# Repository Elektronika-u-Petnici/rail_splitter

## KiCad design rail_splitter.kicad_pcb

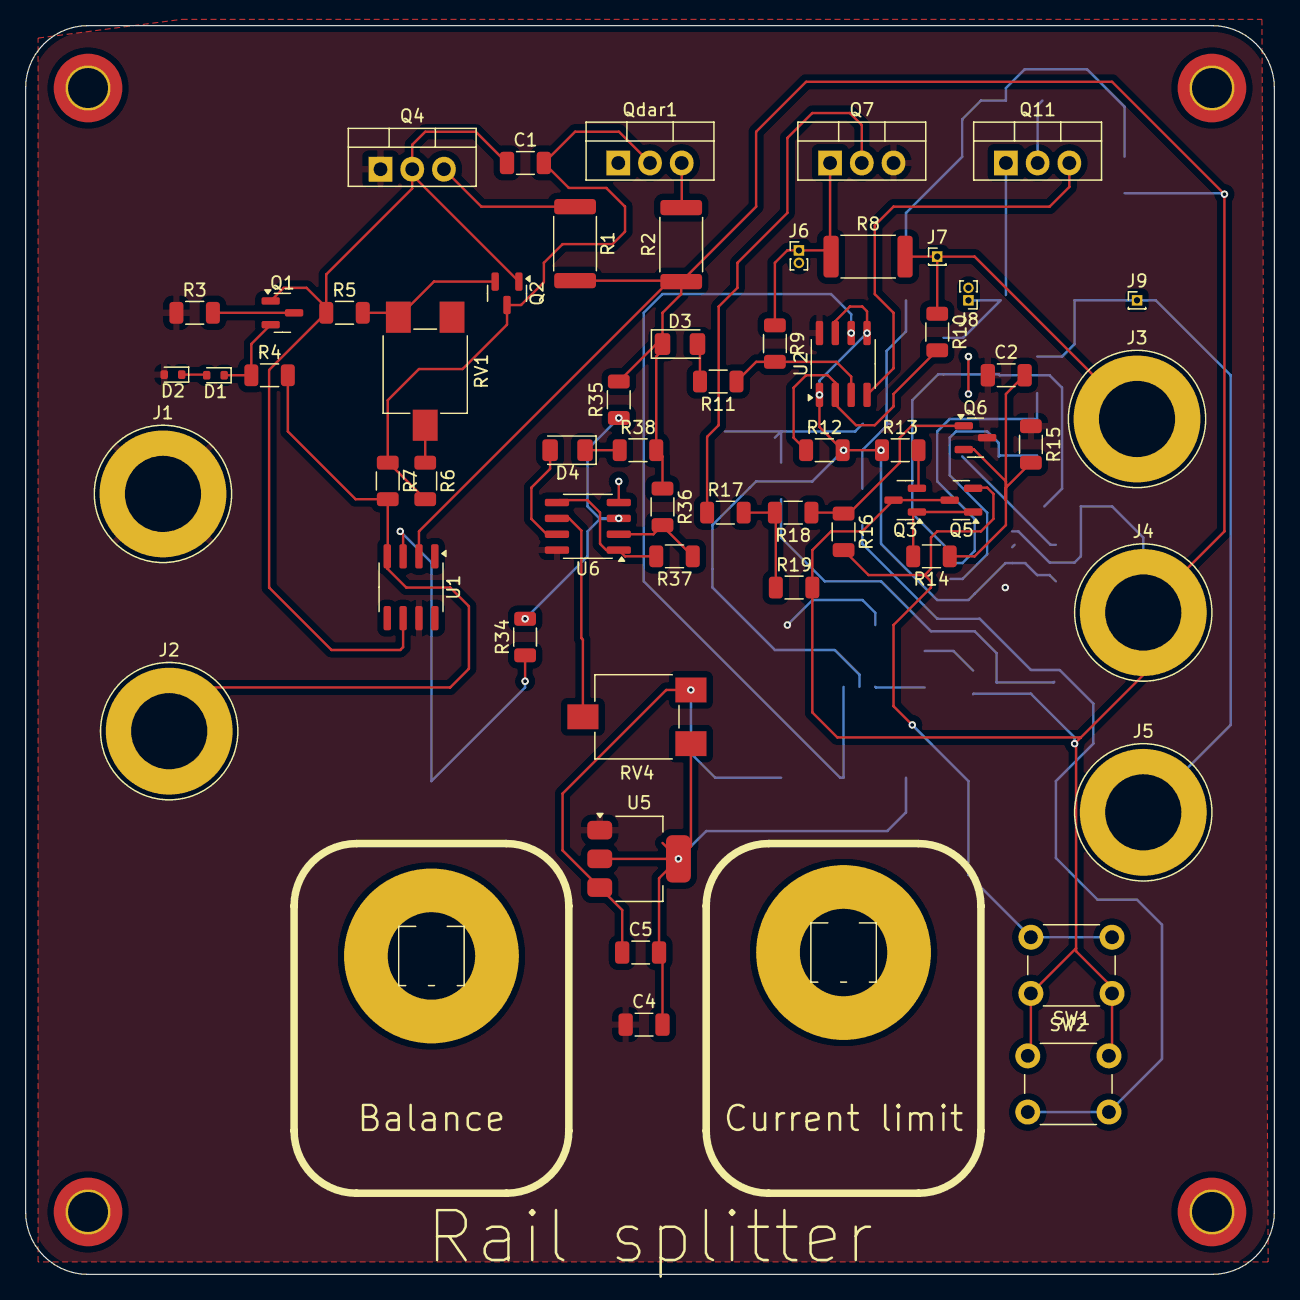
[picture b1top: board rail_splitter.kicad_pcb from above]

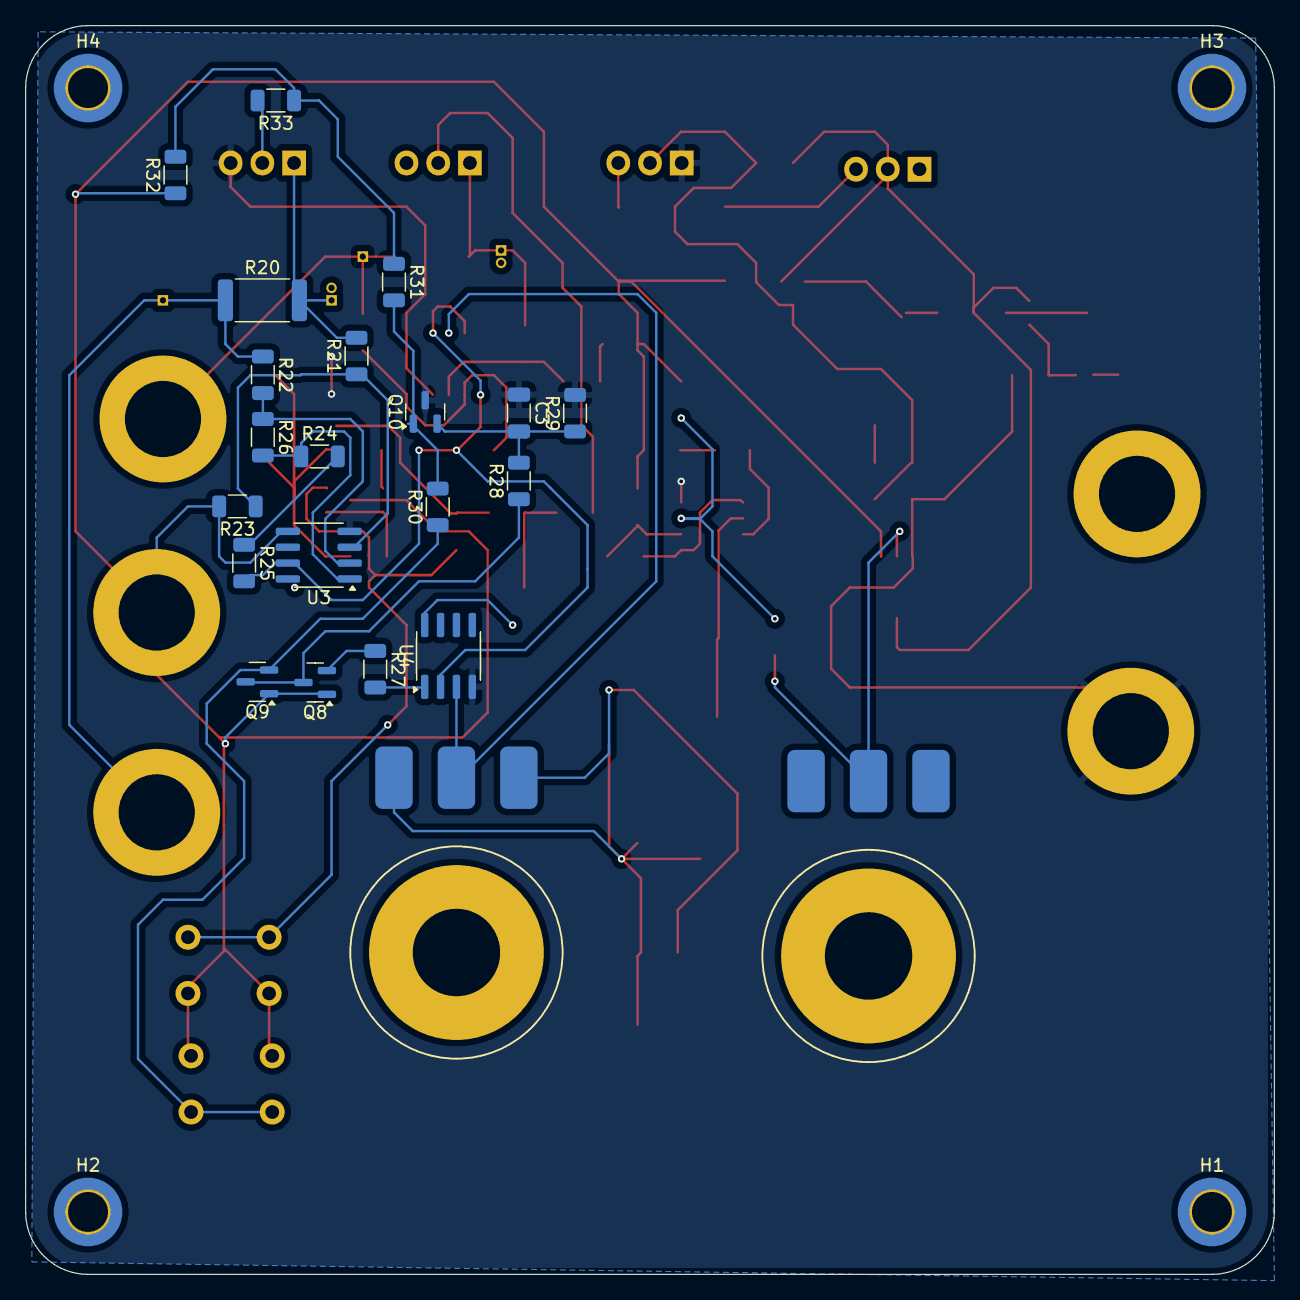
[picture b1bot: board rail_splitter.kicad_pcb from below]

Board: 2 copper layers, 100.0 x 100.0 mm, 84 parts (24 on the bottom side), 49 nets.

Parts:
C1: 10n; C_1206_3216Metric
C2, C3: 0.22u; C_1206_3216Metric
C4: 100n; C_1206_3216Metric
C5: 10u; C_1206_3216Metric
D1, D2: 1N4148WT; D_SOD-523
D3, D4: LED; LED_1206_3216Metric
H1, H2, H3, H4: MountingHole; M3_hole_with_spacer
J1: input +; Banana_Jack_1Pin
J2: input -; Banana_Jack_1Pin
J3: +load; Banana_Jack_1Pin
J4: gnd load; Banana_Jack_1Pin
J5: -load; Banana_Jack_1Pin
J6: shunt+ display pos; PinHeader_1x02_P1.00mm_Vertical
J7: shunt- display pos; PinHeader_1x01_P1.00mm_Vertical
J8: shunt+ display neg; PinHeader_1x02_P1.00mm_Vertical
J9: shunt- display neg; PinHeader_1x01_P1.00mm_Vertical
Q1, Q6, Q8, Q9: PNP; SOT-23
Q2, Q3, Q5, Q10: NPN; SOT-23
Q4: dar; TO-220-3_Vertical
Q7: PMOS; TO-220-3_Vertical
Q11: NMOS; TO-220-3_Vertical
Qdar1: PNP; TO-220-3_Vertical
R1, R2: 0.33; R_2512_6332Metric
R3: 67; R_1206_3216Metric
R4: 5.6k; R_1206_3216Metric
R5: 3.3k; R_1206_3216Metric
R6, R34, R35, R36, R37, R38: 1k; R_1206_3216Metric
R7: 470; R_1206_3216Metric
R8, R20: R; R_2512_6332Metric
R9, R10, R11, R12, R13, R14, R15, R16, R17, R18, R19, R21, R22, R23, R24, R25, R26, R27, R28, R29, R30, R31, R32, R33: R; R_1206_3216Metric
RV1: 1k; Potentiometer_ACP_CA6-VSMD_Vertical
RV2, RV3: R_Potentiometer; front_plate_pot
RV4: R_Potentiometer; Potentiometer_ACP_CA6-VSMD_Vertical
SW1, SW2: SW_Push; SW_PUSH_6mm_H4.3mm
U1: OP07; SOIC-8_3.9x4.9mm_P1.27mm
U2, U3, U4, U6: NE5532; SOIC-8_3.9x4.9mm_P1.27mm
U5: LM2936-3.3; SOT-223-3_TabPin2

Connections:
+3.3V: C5.1, RV3.3, RV4.1, U5.3 (VO)
GND: D3.1 (K), J4.1, Q3.3 (E), Q5.3 (E), Q8.1 (C), Q9.1 (C), R1.2, R2.1, R19.2, R23.2, R32.1, R35.2, R36.1, R38.2, SW1.1, SW2.1, U1.2 (-), U3.5 (+)
GNDD: C4.2, C5.2, RV3.1, RV4.3, U5.2 (GND)
Limit: RV3.2, U2.6 (-), U4.3 (+)
unnamed: D1.2 (A), D2.1 (K)
unnamed: D1.1 (K), Q1.2 (B), R4.1
unnamed: D3.2 (A), R11.2
unnamed: D4.2 (A), U6.7
unnamed: D4.1 (K), R38.1
unnamed: J3.1, J7.1, R8.2, R10.1
unnamed: J5.1, J9.1, R20.1, R22.1
unnamed: J6.1, Q7.1 (D), R8.1, R9.1
unnamed: J8.1, Q11.1 (D), R20.2, R21.2
unnamed: C1.1, Q1.1 (C), Q2.1 (C), Q4.2 (B), R5.1, U1.6
unnamed: Q1.3 (E), R3.2
unnamed: Q2.2 (B), R5.2, RV1.1
unnamed: C1.2, Q2.3 (E), Qdar1.2 (B), R6.2, R7.1
unnamed: Q3.2 (B), R13.2
unnamed: Q3.1 (C), Q5.1 (C), R14.2
unnamed: Q4.3 (E), R1.1
unnamed: Q5.2 (B), R16.2, SW1.2
unnamed: C2.2, Q6.2 (B), R14.1, R15.2
unnamed: Q6.1 (C), R16.1, R18.1
unnamed: Q7.2 (G), R17.1
unnamed: Q8.2 (B), R27.1
unnamed: Q8.3 (E), Q9.3 (E), R28.1
unnamed: Q9.2 (B), R30.1, SW2.2
unnamed: C3.2, Q10.2 (B), R28.2, R29.1
unnamed: Q10.1 (C), R30.2, R31.2
unnamed: Q11.2 (G), R33.2
unnamed: Qdar1.3 (E), R2.2
unnamed: R6.1, RV1.2
unnamed: R17.2, R18.2, R19.1
unnamed: R24.1, R26.2, U3.1
unnamed: R27.2, U4.1
unnamed: R31.1, R32.2, R33.1
unnamed: R34.1, RV2.2, U1.3 (+)
unnamed: R9.2, R11.1, U2.3 (+)
unnamed: R10.2, R12.1, U2.2 (-)
unnamed: R12.2, R13.1, R25.2, U2.1, U2.5 (+), U2.7, U3.7, U4.2 (-)
unnamed: R21.1, R23.1, U3.3 (+)
unnamed: R22.2, R26.1, U3.2 (-)
unnamed: R24.2, R25.1, U3.6 (-)
unnamed: R34.2, R35.1, U6.3 (+)
unnamed: R36.2, R37.1, U6.2 (-)
unnamed: R37.2, U6.1, U6.5 (+)
unnamed: RV4.2, U6.6 (-)
VCC: C2.1, C4.1, D2.2 (A), J1.1, Q4.1 (C), Q6.3 (E), Q7.3 (S), R3.1, R15.1, U1.7 (V+), U2.8 (V+), U3.8 (V+), U4.8 (V+), U5.1 (VI), U6.8 (V+)
VEE: C3.1, J2.1, Q10.3 (E), Q11.3 (S), Qdar1.1 (C), R4.2, R7.2, R29.2, U1.4 (V-), U2.4 (V-), U3.4 (V-), U4.4 (V-), U6.4 (V-)

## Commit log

2025-11-17 Init.
2026-02-18 v1 pcb
2026-03-05 korekcija izgleda, more TBD.
2026-03-06 Sredjena estetika simulacije, dodati komentari.
